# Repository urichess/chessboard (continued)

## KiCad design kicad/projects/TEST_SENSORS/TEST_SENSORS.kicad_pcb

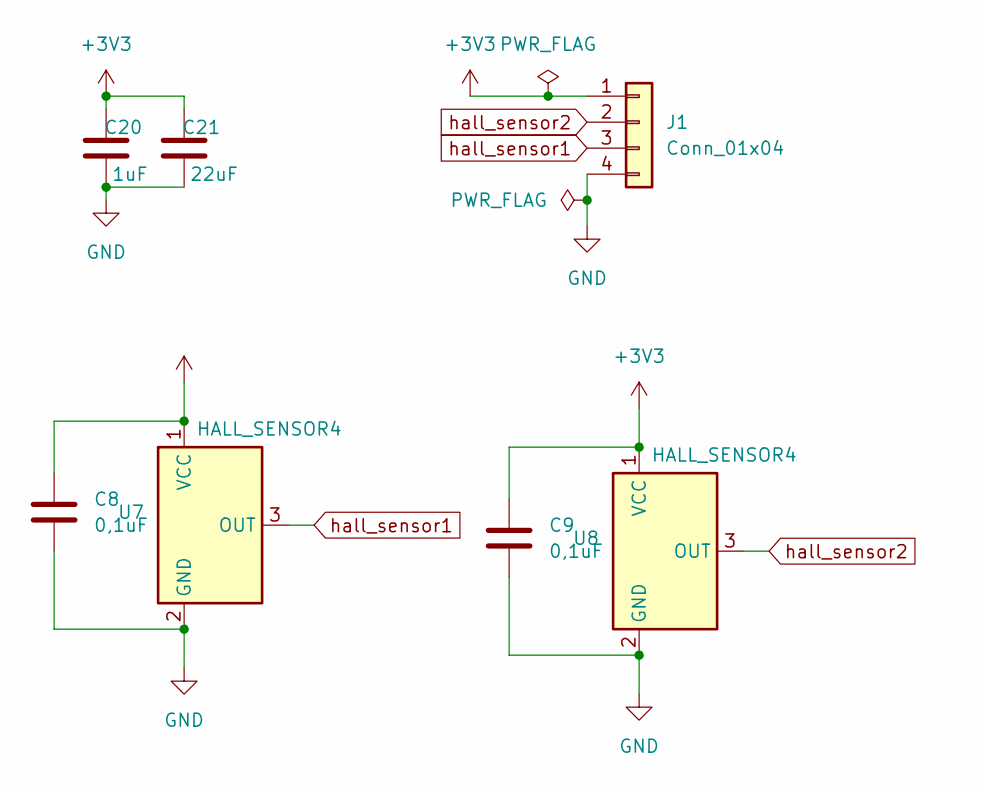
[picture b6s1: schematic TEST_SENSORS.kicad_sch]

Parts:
C8, C9: 0,1uF; C_0805_2012Metric_Pad1.18x1.45mm_HandSolder
C20: 1uF; C_0805_2012Metric_Pad1.18x1.45mm_HandSolder
C21: 22uF; C_0805_2012Metric_Pad1.18x1.45mm_HandSolder
J1: Conn_01x04; PinHeader_1x04_P2.54mm_Vertical
U7, U8: HALL_SENSOR4; TO-92_Inline

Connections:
+3V3: C8.1, C9.1, C20.1, C21.1, J1.1, U7.1 (VCC), U8.1 (VCC)
GND: C8.2, C9.2, C20.2, C21.2, J1.4, U7.2 (GND), U8.2 (GND)
hall_sensor1: J1.3, U7.3 (OUT)
hall_sensor2: J1.2, U8.3 (OUT)

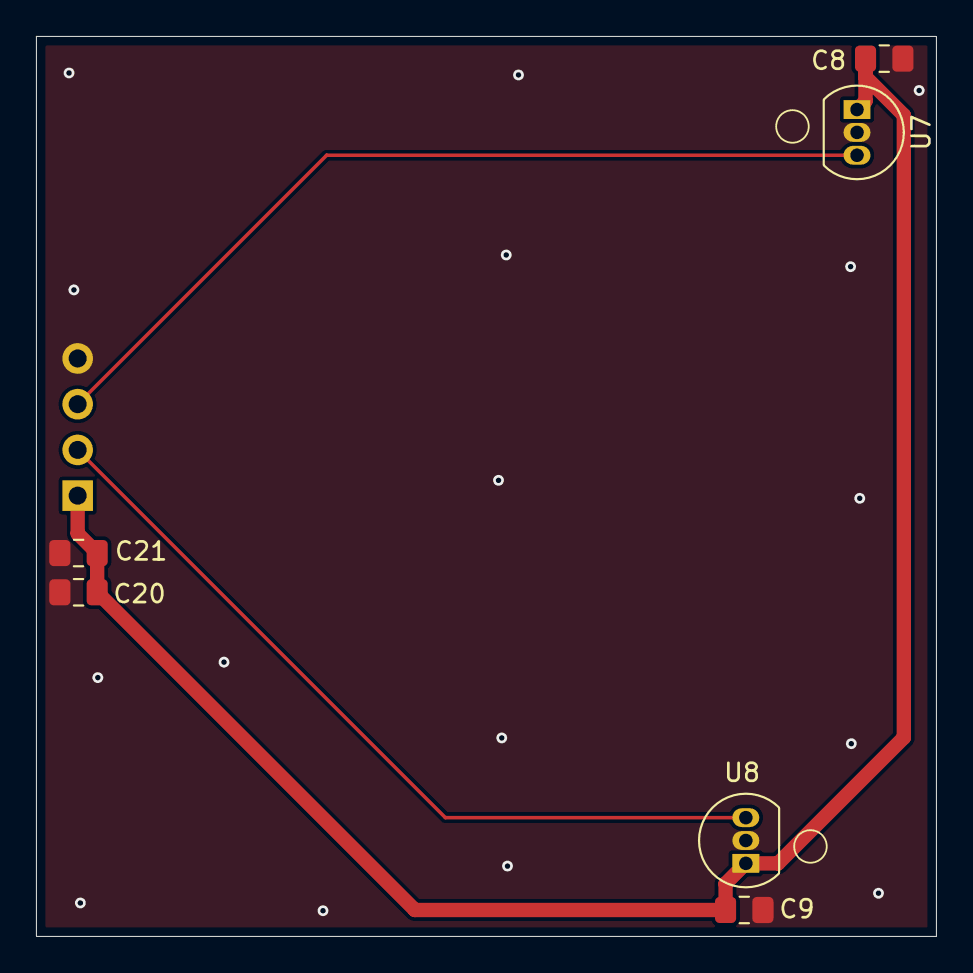
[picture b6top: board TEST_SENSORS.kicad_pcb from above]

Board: 2 copper layers, 50.0 x 50.0 mm, 7 parts (1 on the bottom side), 4 nets.

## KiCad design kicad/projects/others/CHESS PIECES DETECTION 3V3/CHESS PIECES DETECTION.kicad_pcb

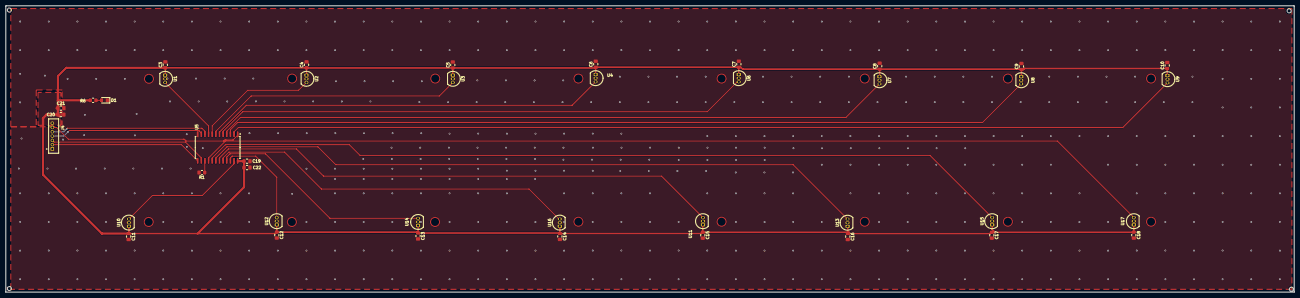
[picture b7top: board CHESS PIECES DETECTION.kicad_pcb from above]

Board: 2 copper layers, 450.0 x 100.0 mm, 41 parts (0 on the bottom side), 25 nets.

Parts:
C3, C4, C5, C6, C7, C8, C9, C10, C11, C12, C13, C14, C15, C16, C17, C18, C19: 0,1uF; C_0805_2012Metric_Pad1.18x1.45mm_HandSolder
C20, C22: 1uF; C_0805_2012Metric_Pad1.18x1.45mm_HandSolder
C21: 22uF; C_0805_2012Metric_Pad1.18x1.45mm_HandSolder
D1: LED_GREEN; LED_0805_2012Metric_Pad1.15x1.40mm_HandSolder
J4: Conn_01x07; JST_B7B-ZR_LF__SN_
R1: 10K; R_0805_2012Metric_Pad1.20x1.40mm_HandSolder
R6: 5.1k; R_0805_2012Metric_Pad1.20x1.40mm_HandSolder
U1: HALL_SENSOR_1; TO-92_Inline
U2: HALL_SENSOR_2; TO-92_Inline
U3: HALL_SENSOR3; TO-92_Inline
U4: HALL_SENSOR4; TO-92_Inline
U5: CD74HC4067M; SOIC-24W_7.5x15.4mm_P1.27mm
U6: HALL_SENSOR_5; TO-92_Inline
U7: HALL_SENSOR_6; TO-92_Inline
U8: HALL_SENSOR7; TO-92_Inline
U9: HALL_SENSOR8; TO-92_Inline
U10: HALL_SENSOR_9; TO-92_Inline
U11: HALL_SENSOR_13; TO-92_Inline
U12: HALL_SENSOR_10; TO-92_Inline
U13: HALL_SENSOR_14; TO-92_Inline
U14: HALL_SENSOR11; TO-92_Inline
U15: HALL_SENSOR15; TO-92_Inline
U16: HALL_SENSOR12; TO-92_Inline
U17: HALL_SENSOR16; TO-92_Inline

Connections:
+3V3: C3.1, C4.1, C5.1, C6.1, C7.1, C8.1, C9.1, C10.1, C11.1, C12.1, C13.1, C14.1, C15.1, C16.1, C17.1, C18.1, C19.1, C20.1, C21.1, C22.1, J4.7, R6.1, U1.1 (VCC), U2.1 (VCC), U3.1 (VCC), U4.1 (VCC), U5.24 (VCC), U6.1 (VCC), U7.1 (VCC), U8.1 (VCC), U9.1 (VCC), U10.1 (VCC), U11.1 (VCC), U12.1 (VCC), U13.1 (VCC), U14.1 (VCC), U15.1 (VCC), U16.1 (VCC), U17.1 (VCC)
GND: C3.2, C4.2, C5.2, C6.2, C7.2, C8.2, C9.2, C10.2, C11.2, C12.2, C13.2, C14.2, C15.2, C16.2, C17.2, C18.2, C19.2, C20.2, C21.2, C22.2, D1.1 (K), J4.1, R1.2, U1.2 (GND), U2.2 (GND), U3.2 (GND), U4.2 (GND), U5.12 (GND), U6.2 (GND), U7.2 (GND), U8.2 (GND), U9.2 (GND), U10.2 (GND), U11.2 (GND), U12.2 (GND), U13.2 (GND), U14.2 (GND), U15.2 (GND), U16.2 (GND), U17.2 (GND)
MUX1: J4.5, U5.10 (S0)
MUX2: J4.4, U5.11 (S1)
MUX3: J4.3, U5.14 (S2)
MUX4: J4.2, U5.13 (S3)
unnamed: D1.2 (A), R6.2
unnamed: R1.1, U5.15 (~E)
Output: J4.6, U5.1 (COM)
hall1: U1.3 (OUT), U5.9 (I0)
hall2: U2.3 (OUT), U5.8 (I1)
hall3: U3.3 (OUT), U5.7 (I2)
hall4: U4.3 (OUT), U5.6 (I3)
hall5: U5.5 (I4), U6.3 (OUT)
hall6: U5.4 (I5), U7.3 (OUT)
hall7: U5.3 (I6), U8.3 (OUT)
hall8: U5.2 (I7), U9.3 (OUT)
hall9: U5.23 (I8), U10.3 (OUT)
hall10: U5.22 (I9), U12.3 (OUT)
hall11: U5.21 (I10), U14.3 (OUT)
hall12: U5.20 (I11), U16.3 (OUT)
hall13: U5.19 (I12), U11.3 (OUT)
hall14: U5.18 (I13), U13.3 (OUT)
hall15: U5.17 (I14), U15.3 (OUT)
hall16: U5.16 (I15), U17.3 (OUT)

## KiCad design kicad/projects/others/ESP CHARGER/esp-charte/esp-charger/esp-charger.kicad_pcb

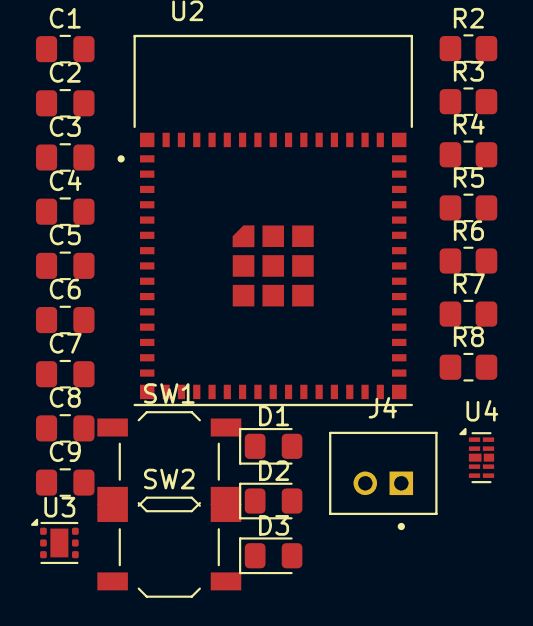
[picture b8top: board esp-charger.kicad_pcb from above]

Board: 2 copper layers, 25 parts (0 on the bottom side), 13 nets, no tracks yet.

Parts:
C1, C2, C3, C4: 1uF; C_0805_2012Metric_Pad1.18x1.45mm_HandSolder
C5: C; C_0805_2012Metric_Pad1.18x1.45mm_HandSolder
C6, C8, C9: 0.1uF; C_0805_2012Metric_Pad1.18x1.45mm_HandSolder
C7: 10uF; C_0805_2012Metric_Pad1.18x1.45mm_HandSolder
D1, D2, D3: LED; LED_0805_2012Metric_Pad1.15x1.40mm_HandSolder
J4: B2B-PH-K-S_LF__SN_; JST_B2B-PH-K-S_LF__SN_
R2: 1M; R_0805_2012Metric_Pad1.20x1.40mm_HandSolder
R3: 200k; R_0805_2012Metric_Pad1.20x1.40mm_HandSolder
R4: 540; R_0805_2012Metric_Pad1.20x1.40mm_HandSolder
R5, R6, R7, R8: 1k; R_0805_2012Metric_Pad1.20x1.40mm_HandSolder
SW1: RESET; SW_SPST_TL3342
SW2: BOOT; SW_SPST_TL3342
U2: ESP32-S3-MINI-1-N8; XCVR_ESP32-S3-MINI-1-N8
U3: TLV75801PDRV; WSON-6-1EP_2x2mm_P0.65mm_EP1x1.6mm
U4: D3V3XA4B10LP; Diodes_UDFN-10_1.0x2.5mm_P0.5mm

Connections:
3V3: C4.1, C6.1, C7.1, R2.1, R7.1, R8.1, U2.3 (3V3), U3.1 (OUT)
5V_IN: C1.1, C5.1, U4.4, U4.7 (NC)
GND: C1.2, C2.2, C3.2, C4.2, C5.2, C6.2, C7.2, C8.2, C9.2, D3.1 (K), J4.2, R3.2, R4.2, SW1.1, SW1.2, SW2.1, SW2.2, U2.1 (GND), U2.2 (GND), U2.42 (GND), U2.43 (GND), U2.46 (GND), U2.47 (GND), U2.48 (GND), U2.49 (GND), U2.50 (GND), U2.51 (GND), U2.52 (GND), U2.53 (GND), U2.54 (GND), U2.55 (GND), U2.56 (GND), U2.57 (GND), U2.58 (GND), U2.59 (GND), U2.60 (GND), U2.61 (GND), U2.61_1 (GND), U2.61_2 (GND), U2.61_3 (GND), U2.61_4 (GND), U2.61_5 (GND), U2.61_6 (GND), U2.61_7 (GND), U2.61_8 (GND), U2.62 (GND), U2.63 (GND), U2.64 (GND), U2.65 (GND), U3.3 (GND), U3.7 (GND)
unnamed: D1.2 (A), R5.2
unnamed: D2.2 (A), R6.2
unnamed: D3.2 (A), R7.2
unnamed: C8.1, R8.2, U2.45 (EN)
unnamed: C9.1, U2.4 (IO0)
unnamed: C2.1, C3.1, J4.1, R5.1, R6.1, U3.4 (EN), U3.6 (IN)
unnamed: R2.2, R3.1, U3.2 (FB)
unnamed: U4.3 (VSS), U4.8 (VSS)
USB_N: U2.23 (IO19), U4.1, U4.10 (NC)
USB_P: U2.24 (IO20), U4.2, U4.9 (NC)

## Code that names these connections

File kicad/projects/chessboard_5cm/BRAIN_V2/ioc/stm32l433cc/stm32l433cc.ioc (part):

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Mcu.Name=STM32L433C(B-C)Tx
Mcu.Package=LQFP48
Mcu.UserName=STM32L433CCTx
PA0.GPIOParameters=GPIO_Label
PA0.GPIO_Label=FBK_3V3_SENSORS
PA0.Signal=ADCx_IN5
PA1.GPIOParameters=GPIO_Label
PA1.GPIO_Label=SIG4
PA1.Signal=GPIO_Analog
PA10.GPIOParameters=GPIO_Label
PA10.GPIO_Label=NRF_CE
PA10.Signal=GPIO_Output
PA11.GPIOParameters=GPIO_Label
PA11.GPIO_Label=USB_N
PA11.Mode=Device
PA11.Signal=USB_DM
PA12.GPIOParameters=GPIO_Label
PA12.GPIO_Label=USB_P
PA12.Mode=Device
PA12.Signal=USB_DP
PA13\ (JTMS-SWDIO).GPIOParameters=GPIO_Label
PA13\ (JTMS-SWDIO).GPIO_Label=SWDATA
PA13\ (JTMS-SWDIO).Mode=Serial_Wire
PA13\ (JTMS-SWDIO).Signal=SYS_JTMS-SWDIO
PA14\ (JTCK-SWCLK).GPIOParameters=GPIO_Label
PA14\ (JTCK-SWCLK).GPIO_Label=SWCLK
PA14\ (JTCK-SWCLK).Mode=Serial_Wire
PA14\ (JTCK-SWCLK).Signal=SYS_JTCK-SWCLK
PA15\ (JTDI).GPIOParameters=GPIO_Label
PA15\ (JTDI).GPIO_Label=LED_USER2
PA15\ (JTDI).Signal=GPIO_Output
PA2.GPIOParameters=GPIO_Label
PA2.GPIO_Label=SIG3
PA2.Signal=GPIO_Analog
PA3.GPIOParameters=GPIO_Label
PA3.GPIO_Label=SIG2
PA3.Signal=GPIO_Analog
PA4.GPIOParameters=GPIO_Label
PA4.GPIO_Label=SIG1
PA4.Signal=GPIO_Analog
PA5.Mode=Full_Duplex_Master
PA5.Signal=SPI1_SCK
PA6.Mode=Full_Duplex_Master
PA6.Signal=SPI1_MISO
PA7.Mode=Full_Duplex_Master
PA7.Signal=SPI1_MOSI
PA8.GPIOParameters=GPIO_Label
PA8.GPIO_Label=HWREV0
PA8.Signal=GPIO_Input
PA9.GPIOParameters=GPIO_Label
PA9.GPIO_Label=HWREV1
PA9.Signal=GPIO_Input
PB0.GPIOParameters=GPIO_Label
PB0.GPIO_Label=NRF_CSN
PB0.Signal=GPIO_Output
PB1.GPIOParameters=GPIO_Label
PB1.GPIO_Label=FBK_3V3_BRAIN
PB1.Signal=ADCx_IN16
PB12.GPIOParameters=GPIO_Label
PB12.GPIO_Label=OUT_3V3
PB12.Signal=GPIO_Output
PB13.GPIOParameters=GPIO_Label
PB13.GPIO_Label=SENSORS_HW_ID0
PB13.Signal=GPIO_Output
PB14.GPIOParameters=GPIO_Label
PB14.GPIO_Label=SENSORS_HW_ID1
PB14.Signal=GPIO_Output
PB15.GPIOParameters=GPIO_Label
PB15.GPIO_Label=SENSORS_HW_ID2
PB15.Signal=GPIO_Output
PB2.GPIOParameters=GPIO_Label
PB2.GPIO_Label=NRF_IRQ
PB2.Signal=GPIO_Output
PB3\ (JTDO-TRACESWO).GPIOParameters=GPIO_Label
PB3\ (JTDO-TRACESWO).GPIO_Label=LED_USER1
PB3\ (JTDO-TRACESWO).Signal=GPIO_Output
PB4\ (NJTRST).GPIOParameters=GPIO_Label
PB4\ (NJTRST).GPIO_Label=LED_ALIVE
PB4\ (NJTRST).Signal=GPIO_Output
PB5.GPIOParameters=GPIO_Label
PB5.GPIO_Label=BUZZER_PWM
PB5.Signal=GPIO_Output
PB6.Mode=Asynchronous
PB6.Signal=USART1_TX
PB7.Mode=Asynchronous
PB7.Signal=USART1_RX
PB8.Mode=I2C
PB8.Signal=I2C1_SCL
PB9.Mode=I2C
PB9.Signal=I2C1_SDA
PC13.GPIOParameters=GPIO_Label
PC13.GPIO_Label=MUX1
PC13.Signal=GPIO_Output
PC14-OSC32_IN\ (PC14).GPIOParameters=GPIO_Label
PC14-OSC32_IN\ (PC14).GPIO_Label=MUX2
PC14-OSC32_IN\ (PC14).Signal=GPIO_Output
PC15-OSC32_OUT\ (PC15).GPIOParameters=GPIO_Label
PC15-OSC32_OUT\ (PC15).GPIO_Label=MUX3
PC15-OSC32_OUT\ (PC15).Signal=GPIO_Output
PH0-OSC_IN\ (PH0).GPIOParameters=GPIO_Label
PH0-OSC_IN\ (PH0).GPIO_Label=MUX4
PH0-OSC_IN\ (PH0).Signal=GPIO_Output
PH1-OSC_OUT\ (PH1).GPIOParameters=GPIO_Label
PH1-OSC_OUT\ (PH1).GPIO_Label=SENSORS_REV0
PH1-OSC_OUT\ (PH1).Signal=GPIO_Output
PH3-BOOT0.GPIOParameters=GPIO_Label
PH3-BOOT0.GPIO_Label=SENSORS_REV1
PH3-BOOT0.Signal=GPIO_Output
RCC.HSE_VALUE=8000000
RCC.SYSCLKFreq_VALUE=80000000
RCC.SYSCLKSource=RCC_SYSCLKSOURCE_PLLCLK
board=custom

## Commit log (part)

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2024-08-11 ignore build directory
2024-08-11 ignoring build directory
2024-08-13 tentative test of wifi with arduino...
2024-08-17 trying to debug minimal
2024-08-17 debug is working. led blinks and breakpoints work
2024-08-20 last advances
2024-08-22 drawing
2024-08-22 drawing rpi pico w
2024-08-24 adding rpi pico w board
2024-09-14 uart shell and console working at last!
2025-05-30 description
2025-06-15 compiling for arduino. ignoring wifi features
2025-06-15 remove callWest
2025-06-15 Revert "remove callWest"
    This reverts commit cb0af75475b28aa91090f0b24788513788c0cd40.
2025-06-16 basic example of threads, logging and led working on both arduino and nucleo_g474re
2025-06-16 ignoring config_default. all set to work with cubeide!!
2025-06-18 reading ADCs!
2025-06-18 reading 4 adcs and configuring mux gpios. not tested..
    Ready to read board?
2025-06-18 writting muxs. pending to test
2025-06-19 reading all sensors...
2025-06-20 reading sensors, converting to gauss and filtering to get occupancy
2025-06-25 reading the sensors matrix
2025-06-25 enabled shell
2025-06-25 enabled logging
2025-06-25 fine tunning logs
2025-06-25 adding uart3 and more fine tunning
2025-06-25 enabled second uart to send board position
2025-06-26 sending positions to uart in a separate thread
2025-06-26 creating folder for client
2025-06-26 Add Python dependencies
2025-06-26 python environment
2025-06-26 installiny python chess
2025-06-26 use chess python to show the board
2025-06-26 placeholdsr
2025-06-26 replacing things
2025-06-26 more relocations
2025-06-26 python works and shows the board!!
2025-06-27 renaming folders
2025-06-27 updating readme
2025-06-27 renaming venv
2025-06-27 changed a couple of things related to filtering and trasposing matrixes
2025-07-02 application understanding positions
2025-07-03 detecting moves.. caputre fails? tools for testing
2025-07-04 following pieces work with normal moves, captures and castles
2025-07-05 installing berserk
2025-07-05 small program able to connect lichess, show personal data an list ongoing games
2025-07-09 game menu and serial handler
2025-07-09 remaning
2025-07-10 lichess connector works
2025-07-11 gameplay logic. only pending final adjustments to BoardSerial
2025-07-11 finished
2025-07-11 rename and cleanup
2025-07-11 more cleans
2025-07-11 tested basic game logic
2025-07-12 fixes and monitoring to test with serial
2025-07-12 reorganized
2025-07-12 increased tests
2025-07-12 adding promotion test. promotion fails
2025-07-12 rename
2025-07-12 promotion works! always queen...
2025-07-13 print improvements
2025-07-13 some ui examples
2025-07-14 enable serial choosing via params
2025-07-18 examples to simulate ili9341 with tk
2025-07-19 little refactor
2025-07-19 can get voltage and gauss from shell
2025-07-21 flash calibratons logic, not tested
2025-07-21 calibs in flash ok, pieces detection fast, everything nice
2025-07-22 last refiements
2025-07-22 some thoughts about what's next
2025-07-22 updating todo
2025-07-22 better formatting
2025-07-23 removing vscode
2025-07-23 Scoped lock
2025-07-23 cleaning code
2025-07-23 calibration warning
2025-07-23 fixed the 0s not working and calibrations problem
2025-07-23 updated todo
2025-07-26 datasheets
2025-07-29 android application
2025-09-22 old pending changes of android app..
2025-09-22 old changes of android
2025-09-22 supporting custom chessbrain board
2025-09-29 initialize 3v3 pin to enabled on boot
2025-10-02 sending uart output to ESP which bridges it to USB
2025-10-04 modifying calibs limits
2025-10-04 modifying calibs limits (#9)
2025-10-04 board inversion ability, ready to play with board upside down
2025-10-04 board inversion ability, ready to play with board upside down (#10)
2025-10-04 using LSE clock
2025-10-04 beautiful comments
2025-10-05 improving calibrations waitting correct time after mux changes fine tuning histeresis...
2025-10-05 print gausses matrix command useful for debugging
2025-10-05 increase mux wait since change from black to white in consecutive squares are affected with 3ms
2025-10-05 improving calibrations (#13)
    * improving calibrations
    waitting correct time after mux changes
    fine tuning histeresis...
    * print gausses matrix command useful for debugging
    * increase mux wait since change from black to white in consecutive squares are affected with 3ms
2025-10-05 using LSE clock (#11)
    * using LSE clock
    * beautiful comments
2025-10-05 minimum histeresis because of so good calibrations
2025-10-06 using orange led to see when a movement has been detected. better said when there is uart communication
2025-10-06 slowest pieces detection is 250ms
2025-10-06 slowest pieces detection is 250ms (#14)
2025-10-06 uart usb ble bridge
2025-10-06 fixing bridge
2025-10-07 improving esp32 uart-usb-bluetooth bridge
2025-10-11 android files
2025-10-11 1. opponent's piece can be taken before player's in case of capture 2. improved messages, more clear 3. fixed a bug after recovering from wrong position, current_position was not updated
2025-10-12 fixed serial input unwanted synchronizing tells wrong squares
2025-10-12 when update from board is not received, all squares are considered wrong
2025-10-12 improving move detection (#18)
    * 1. opponent's piece can be taken before player's in case of capture
    2. improved messages, more clear
    3. fixed a bug after recovering from wrong position, current_position was not updated
    4. synchronizing tells wrong squares
    5. unwanted data in serial is discarted automatically
    * fixed serial input unwanted
2025-10-13 resending last message if receiving REQUEST:1
2025-10-13 sending request:1 te receive current position of board
2025-10-14 resending last message if receiving REQUEST:1 (#21)
    * resending last message if receiving REQUEST:1
    * sending request:1 te receive current position of board
2025-10-15 ui examples. choosing kivy
2025-10-15 adding kivy to requerminets
2025-10-16 build android app with kivy
2025-10-16 calculadora example
2025-10-16 main traces to see if bind succeeded
2025-10-16 state library and example of workflow
2025-10-17 empty ui for chess app
2025-10-17 chessapp main
2025-10-17 start game screen with serial and token
2025-10-17 transition to chess game sceen
2025-10-18 adding a workflow manager
2025-10-18 moving workflow manager in independent file
2025-10-18 using kivy events to comunicate workflow manager with screens
2025-10-18 game logic is called from ui
2025-10-19 separate game logic and leave screens ready to use
2025-10-19 refreshing last move and time pending: increment, names, elo and colors
2025-10-20 preparing to send several message types in callback
2025-10-20 show minimal game info and unlimited time
2025-10-20 show elo and gameid and status
2025-10-20 board sync request and detection when remote player moves
2025-10-20 string change
2025-10-20 game dynamic working well
2025-10-20 fix color
2025-10-20 fixing a couple of colors
2025-10-21 better way of indicating last moves
2025-10-21 better way of indicating turn
2025-10-21 nive turn and colors notifications
2025-10-21 attaching to a game in background. not yet creating new games.
2025-10-21 First UI (#27)
    * ui examples. choosing kivy
    * adding kivy to requerminets
    * build android app with kivy
    * calculadora example
    * main traces to see if bind succeeded
    * state library and example of workflow
2025-10-22 adding wait screen
2025-10-22 separated config screen
2025-10-22 adding new screen for game creation. still useless
2025-10-22 create game binds cancel
2025-10-22 improving create game screen so much
2025-10-23 sending game creation data to game logic. ready to talk to lichess api and create real game!!
2025-10-23 challenges creation work ok against stockfish
2025-10-23 all types of game can be created
2025-10-24 handle end of game. no button to return to menu yet
2025-10-24 fixing rated
2025-10-24 UI delivery2 (#31)
    * adding wait screen
    * separated config screen
    * adding new screen for game creation. still useless
    * create game binds cancel
    * improving create game screen so much
    * sending game creation data to game logic. ready to talk to lichess api and create real game!!
2025-10-24 ignore config file
2025-10-26 first try not working
2025-10-26 working signed fw with mcuboot. problem: 95% of partition used....
2025-10-26 reducing flash usage to 88%...
2025-10-26 versioning
2025-10-27 Add MCUboot as submodule
2025-10-27 removing files
2025-10-27 mcuboot integration and buildall script
2025-10-27 do not modify mcuboot, pass a param instead
2025-10-27 fine tuning
2025-10-27 mcumgr compiled not tested
2025-10-28 configuring updater mode
2025-10-28 adding upgrader app
2025-10-29 overlays and device tree tunned
2025-10-30 update simulation compiles...
2025-10-30 fixing slot partition addresses
2025-11-01 disable secure boot
2025-11-02 mcuboot + app + upgrader partitions (#48)
    * first try not working
    * working signed fw with mcuboot. problem: 95% of partition used....
    * reducing flash usage to 88%...
    * versioning
    * Add MCUboot as submodule
    * removing files
2026-01-20 removing chessapp python as it has its own repo now
2026-01-20 removing chess app as it has its own repo
